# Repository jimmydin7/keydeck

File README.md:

# Keydeck
---
A hardware macropad designed entirely from scratch, including the PCB, schematic, routing, and 3D modeling
---
|||
|----------|------------|
|  |  |

| 3D Model | PCB Layout |
|----------|------------|
|  |  |

| Case Day| Case Night|
|---------|------------|
|  |  |

# BOM

- XIAO RP2040 (1) 
- EC11 Encoder (1) 
- Switches (5) 
- Keycaps (5)
- smd leds sk6812min (2)

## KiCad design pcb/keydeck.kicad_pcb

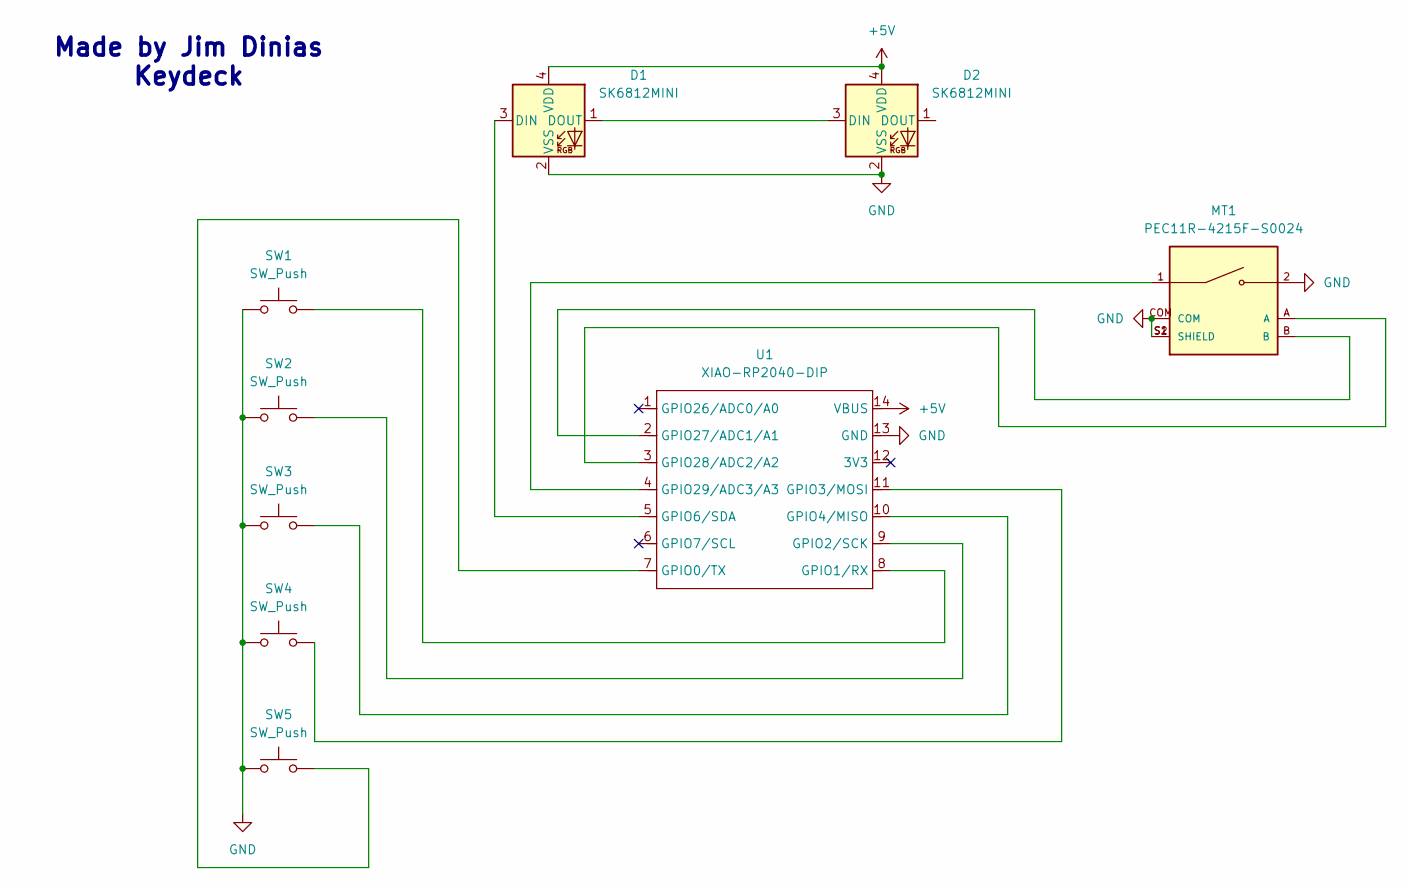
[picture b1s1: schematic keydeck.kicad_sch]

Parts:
D1, D2: SK6812MINI; LED_SK6812MINI_PLCC4_3.5x3.5mm_P1.75mm
MT1: PEC11R-4215F-S0024; XDCR_PEC11R-4215F-S0024; PARTREV Rev. 09/19
SW1, SW2, SW3, SW4, SW5: SW_Push; SW_Cherry_MX_1.00u_PCB
U1: XIAO-RP2040-DIP

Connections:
+5V: D1.4 (VDD), D2.4 (VDD), U1.14 (VBUS)
GND: D1.2 (VSS), D2.2 (VSS), MT1.2, MT1.COM, MT1.S1 (SHIELD), MT1.S2 (SHIELD), SW1.1, SW2.1, SW3.1, SW4.1, SW5.1, U1.13 (GND)
unnamed: D1.3 (DIN), U1.5 (GPIO6/SDA)
unnamed: D1.1 (DOUT), D2.3 (DIN)
unnamed: SW5.2, U1.7 (GPIO0/TX)
unnamed: SW1.2, U1.8 (GPIO1/RX)
unnamed: SW2.2, U1.9 (GPIO2/SCK)
unnamed: SW4.2, U1.11 (GPIO3/MOSI)
unnamed: SW3.2, U1.10 (GPIO4/MISO)
unnamed: MT1.B, U1.2 (GPIO27/ADC1/A1)
unnamed: MT1.A, U1.3 (GPIO28/ADC2/A2)
unnamed: MT1.1, U1.4 (GPIO29/ADC3/A3)

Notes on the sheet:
Made by Jim Dinias Keydeck

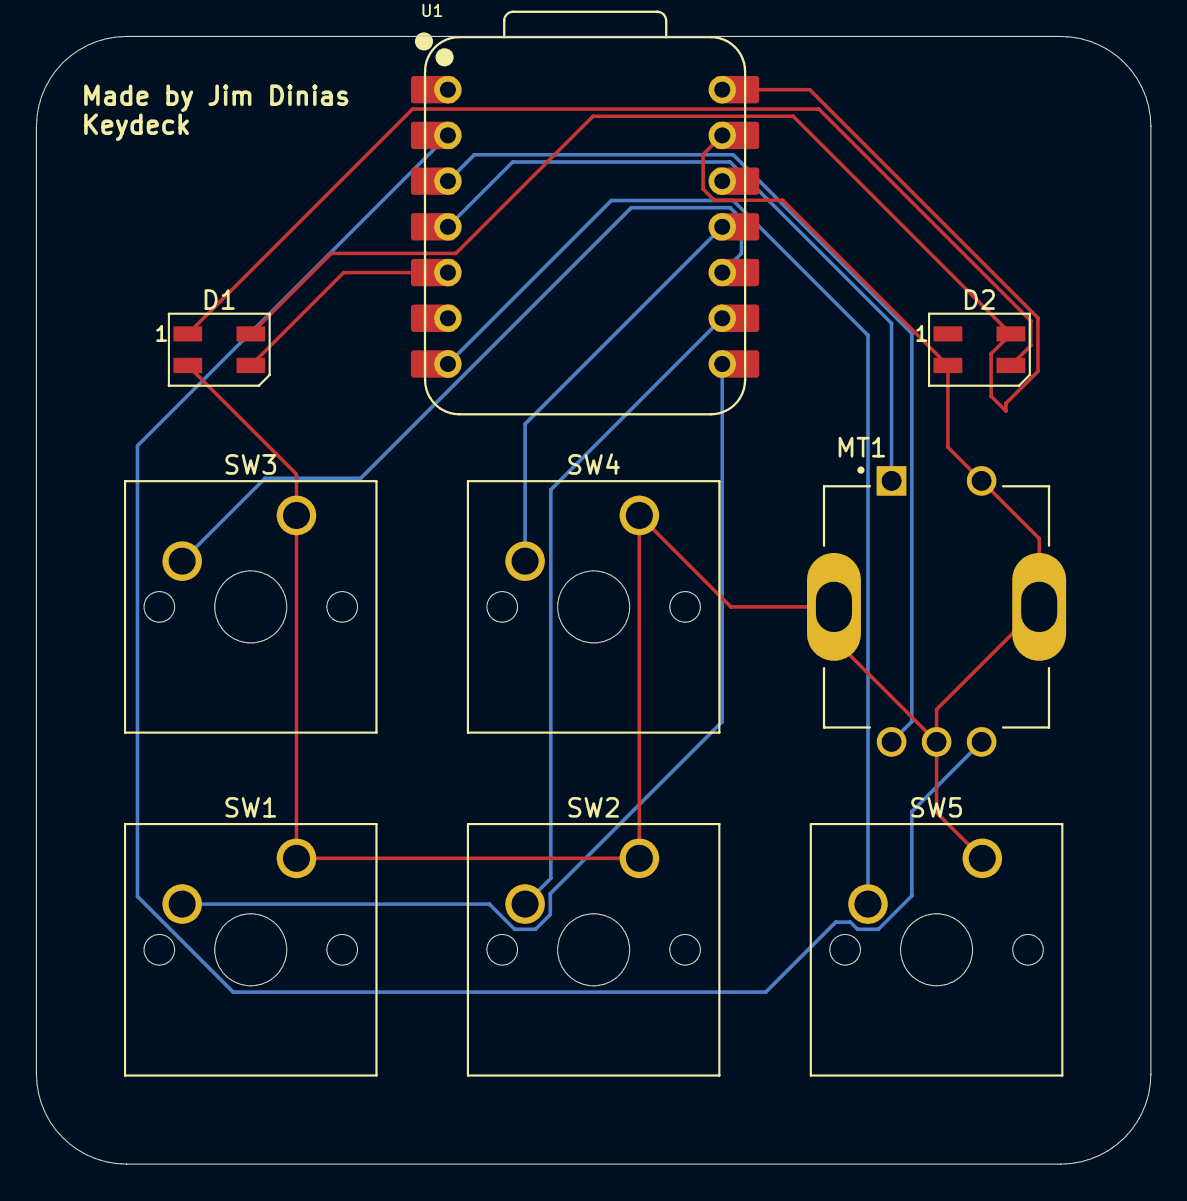
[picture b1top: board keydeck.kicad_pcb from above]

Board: 2 copper layers, 61.9 x 62.6 mm, 9 parts (0 on the bottom side), 12 nets.

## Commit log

2025-08-07 fix: fix structure
2025-08-08 add round edges + new gerber
2025-08-08 round edges on pcb & fix 90 degrees routing
2025-08-09 new gerber zip
2025-08-10 add bom
2025-08-16 add 3d printed case
2025-09-27 add completed photos
2025-09-27 new images!
